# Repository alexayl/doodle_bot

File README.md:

# Doodle Bot

DoodleBot device for autonomous whiteboard management.

This repository is setup as a **monorepo** that contains the code for the different subsystems that are flashed to different devices. Please see the links below for each subsystems' README:

- [Firmware](firmware/README.md) (Alex Aylward and Jain Iftesam) is responsible for all of the code on the device.
- [CV Software](cv_software/README.md) (Trevor Antle is responsible for developing the Computer Vision application
- [Pathfinding](pathfinding/README.md) (Tom Concannon) is responsible for the path generation algorithm

## Setup

### Docs

Requirements: graphviz

### Firmware

_Note: If you are on a PC, Zephyr does not work well with WSL. Please use Windows native, or consider eventually dual-booting/VM linux!_

1. Install prerequisites

    - [Python3](https://www.geeksforgeeks.org/python/download-and-install-python-3-latest-version/)

    - Complete **only** the [Install Dependencies](https://docs.zephyrproject.org/latest/develop/getting_started/index.html#install-dependencies) section of the [Getting Started Guide](https://docs.zephyrproject.org/latest/develop/getting_started/index.html#getting-started-guide).

    - [Just command runner](https://github.com/casey/just?tab=readme-ov-file#installation) - This is used like a makefile as a hotkey for all of our project-specific commands
        - If you are using Windows, installing chocolatey package manager is recommended. After installing chocolatey, you can install just by running `choco install just`.
        - If you are on Mac, use the [Homebrew](https://brew.sh/) command `brew install just`.

If building/flsahing for [nrf52840 dk](https://docs.zephyrproject.org/latest/boards/nordic/nrf52840dk/doc/index.html):
    - SEGGER J-Link DLL
    - nrfutil (there is a python lib that allegedly has it; I needed to install it from the website though due to python dependency version conflicts)
    - 
2. Clone this repository:
    ```bash
    git clone git@github.com:alexayl/doodle_bot.git
    cd doodle_bot
    ```

3. Create and activate a Python virtual environment:
    ```bash
    python -m venv .venv
    
    source .venv/bin/activate     # Linux/macOS
    .venv\Scripts\activate.bat    # PC, Command Prompt
    .venv\Scripts\Activate.ps1    # PC, Powershell
    source .venv/Scripts/activate # PC. Git bash
    ```

4. Install west
    ```bash
    pip install west
    ```

5. Update the workspace
    ```bash
    cd firmware
    west update
    west packages pip --install
    ```

6. Install the Zephyr SDK
    1. navigate to `doodle_bot/firmware/zephyr`
        ```bash
        cd zephyr
        ```
    2.  Perform installation 
        ```bash
        west sdk install
        ```

7. Try to build and run
    1. navigate to `doodle_bot/firmware`
        ```bash
        cd ..
        ```
    2.  Build the sim to verify it works 
        ```bash
        just run-sim
        ```

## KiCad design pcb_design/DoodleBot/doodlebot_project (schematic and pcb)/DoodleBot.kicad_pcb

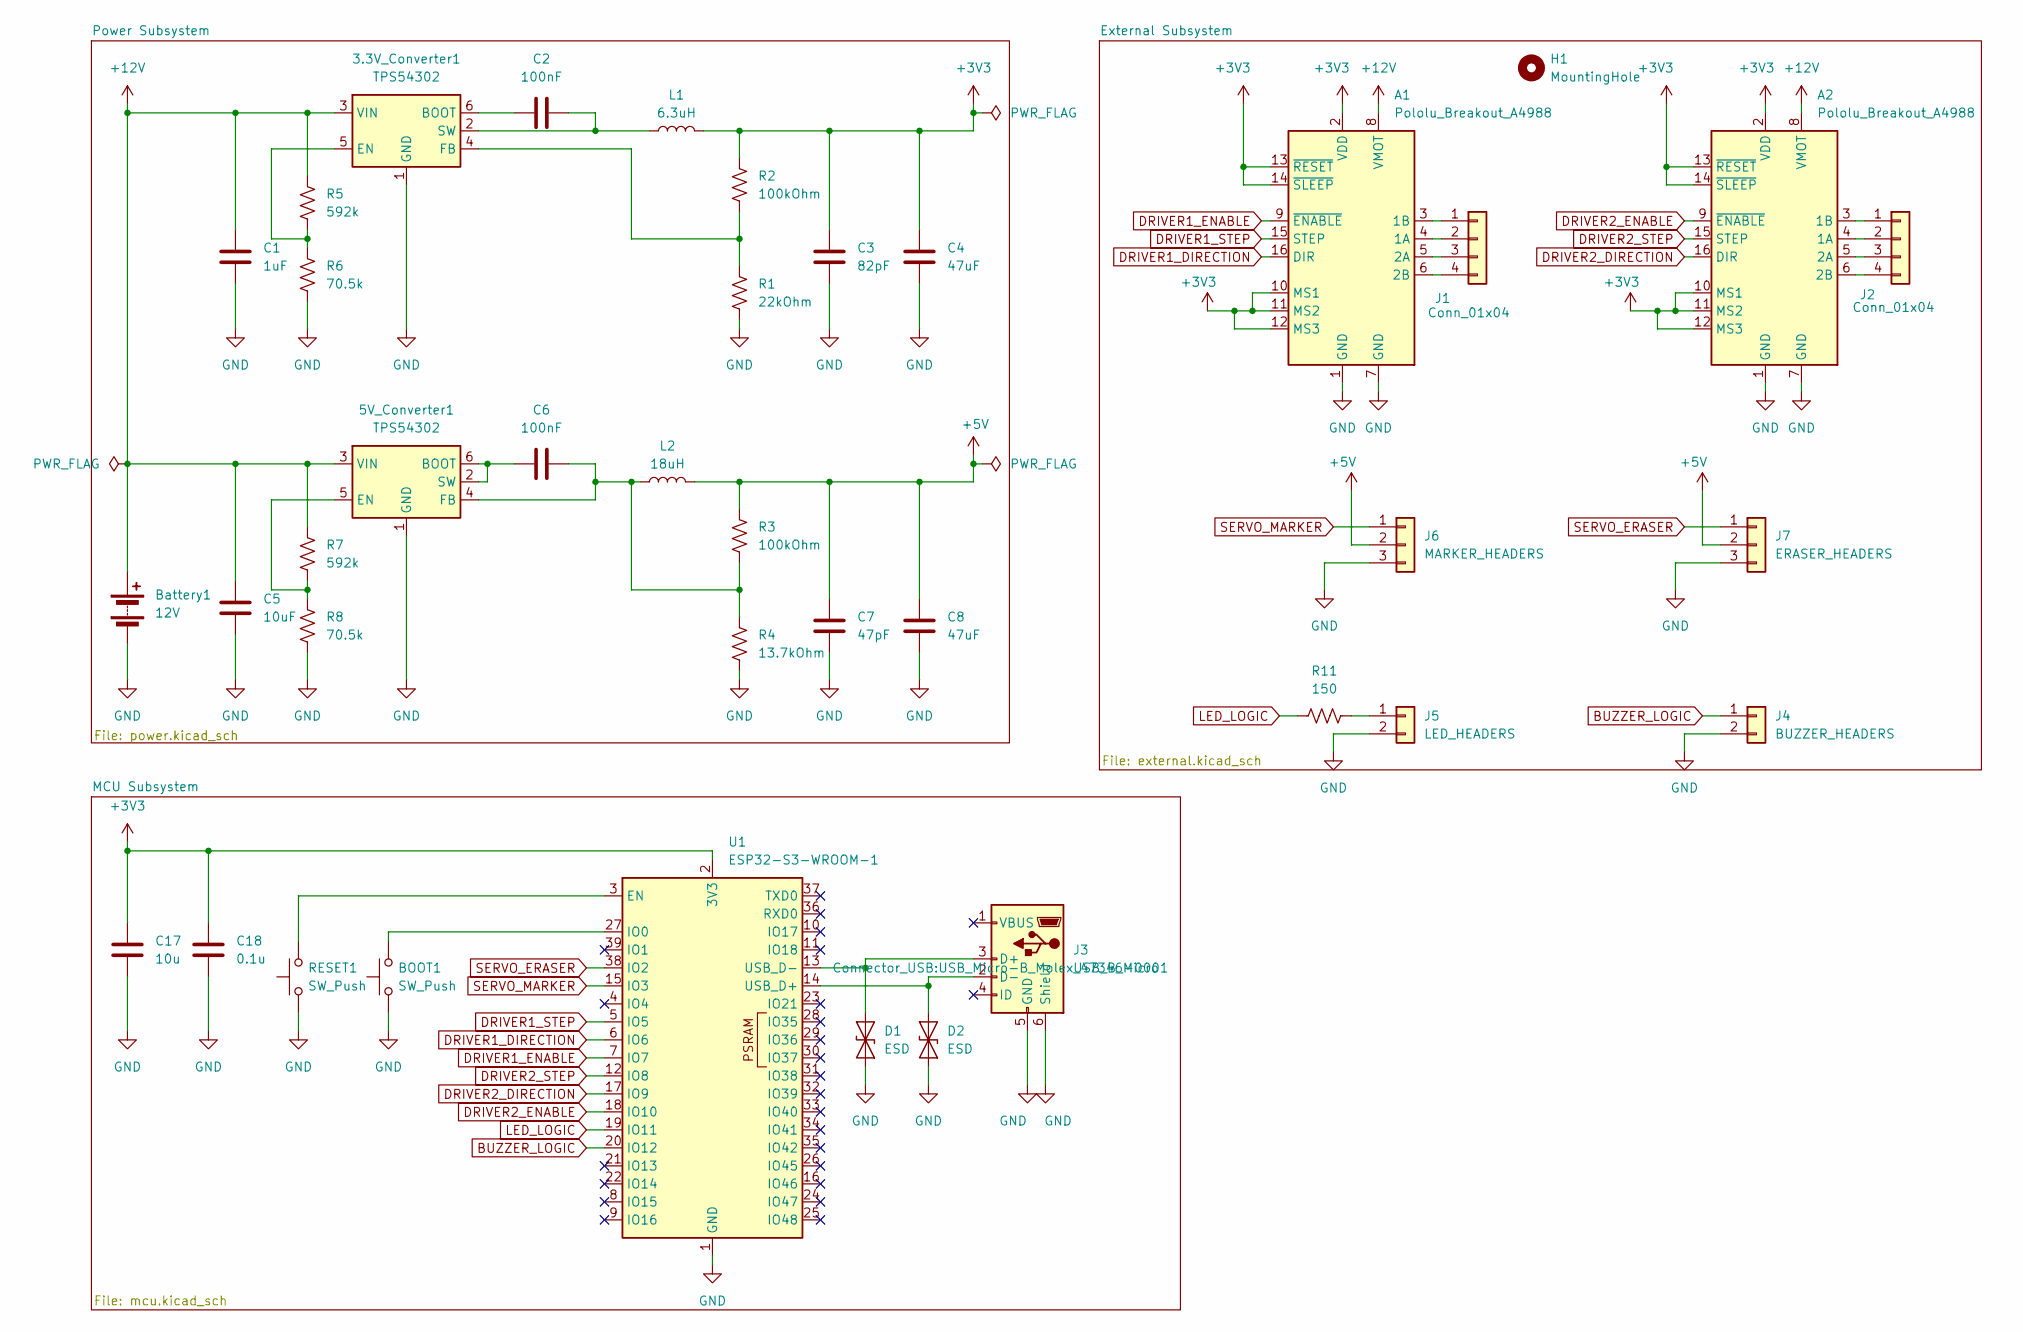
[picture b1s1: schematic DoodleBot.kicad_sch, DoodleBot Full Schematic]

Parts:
3.3V_Converter1, 5V_Converter1: TPS54302; SOT-23-6
A1, A2: Pololu_Breakout_A4988; Pololu_Breakout-16_15.2x20.3mm
BOOT1: SW_Push; SW_SPST_PTS647_Sx38
Battery1: 12V; PinHeader_1x02_P2.54mm_Vertical
C1: 1uF; C_0603_1608Metric
C2, C6: 100nF; C_0603_1608Metric
C3: 82pF; C_0603_1608Metric
C4, C8: 47uF; C_0603_1608Metric
C5: 10uF; C_0603_1608Metric
C7: 47pF; C_0603_1608Metric
C17: 10u; C_0603_1608Metric
C18: 0.1u; C_0603_1608Metric
D1, D2: ESD; D_0603_1608Metric
H1: MountingHole; MountingHole_2mm
J1, J2: Conn_01x04; PinHeader_1x04_P2.54mm_Vertical
J3: USB_B_Micro; USB_Micro-B_Molex_47346-0001
J4: BUZZER_HEADERS; PinHeader_1x02_P2.54mm_Vertical
J5: LED_HEADERS; PinHeader_1x02_P2.54mm_Vertical
J6: MARKER_HEADERS; PinHeader_1x03_P2.54mm_Vertical
J7: ERASER_HEADERS; PinHeader_1x03_P2.54mm_Vertical
L1: 6.3uH; L_Radial_D6.0mm_P4.00mm
L2: 18uH; L_Radial_D6.0mm_P4.00mm
R1: 22kOhm; R_0603_1608Metric
R2, R3: 100kOhm; R_0603_1608Metric
R4: 13.7kOhm; R_0603_1608Metric
R5, R7: 592k; R_0603_1608Metric
R6, R8: 70.5k; R_0603_1608Metric
R11: 150; R_0603_1608Metric
RESET1: SW_Push; SW_SPST_PTS647_Sx38
U1: ESP32-S3-WROOM-1

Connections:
+3V3: A1.2 (VDD), A1.10 (MS1), A1.11 (MS2), A1.12 (MS3), A1.13 (~RESET), A1.14 (~SLEEP), A2.2 (VDD), A2.10 (MS1), A2.11 (MS2), A2.12 (MS3), A2.13 (~RESET), A2.14 (~SLEEP), C3.2, C4.2, C17.1, C18.1, L1.2, R2.1, U1.2 (3V3)
+5V: C7.2, C8.2, J6.2, J7.2, L2.2, R3.1
+12V: 3.3V_Converter1.3 (VIN), 5V_Converter1.3 (VIN), A1.8 (VMOT), A2.8 (VMOT), Battery1.1 (+), C1.1, C5.1, R5.1, R7.1
BUZZER_LOGIC: J4.1, U1.20 (IO12)
DRIVER1_DIRECTION: A1.16 (DIR), U1.6 (IO6)
DRIVER1_ENABLE: A1.9 (~ENABLE), U1.7 (IO7)
DRIVER1_STEP: A1.15 (STEP), U1.5 (IO5)
DRIVER2_DIRECTION: A2.16 (DIR), U1.17 (IO9)
DRIVER2_ENABLE: A2.9 (~ENABLE), U1.18 (IO10)
DRIVER2_STEP: A2.15 (STEP), U1.12 (IO8)
GND: 3.3V_Converter1.1 (GND), 5V_Converter1.1 (GND), A1.1 (GND), A1.7 (GND), A2.1 (GND), A2.7 (GND), BOOT1.1, Battery1.2 (-), C1.2, C3.1, C4.1, C5.2, C7.1, C8.1, C17.2, C18.2, D1.1 (A1), D2.1 (A1), J3.5 (GND), J3.6 (Shield), J4.2, J5.2, J6.3, J7.3, R1.2, R4.2, R6.2, R8.2, RESET1.1, U1.1 (GND), U1.40 (GND), U1.41 (GND)
LED_LOGIC: R11.1, U1.19 (IO11)
unnamed: 3.3V_Converter1.6 (BOOT), C2.1
unnamed: 3.3V_Converter1.5 (EN), R5.2, R6.1
unnamed: 3.3V_Converter1.4 (FB), R1.1, R2.2
unnamed: 3.3V_Converter1.2 (SW), C2.2, L1.1
unnamed: 5V_Converter1.2 (SW), 5V_Converter1.6 (BOOT), C6.1
unnamed: 5V_Converter1.5 (EN), R7.2, R8.1
unnamed: 5V_Converter1.4 (FB), C6.2, L2.1, R3.2, R4.1
unnamed: A1.4 (1A), J1.2
unnamed: A1.3 (1B), J1.1
unnamed: A1.5 (2A), J1.3
unnamed: A1.6 (2B), J1.4
unnamed: A2.4 (1A), J2.2
unnamed: A2.3 (1B), J2.1
unnamed: A2.5 (2A), J2.3
unnamed: A2.6 (2B), J2.4
unnamed: D1.2 (A2), J3.3 (D+), U1.13 (USB_D-)
unnamed: D2.2 (A2), J3.2 (D-), U1.14 (USB_D+)
unnamed: J5.1, R11.2
unnamed: RESET1.2, U1.3 (EN)
unnamed: BOOT1.2, U1.27 (IO0)
SERVO_ERASER: J7.1, U1.38 (IO2)
SERVO_MARKER: J6.1, U1.15 (IO3)

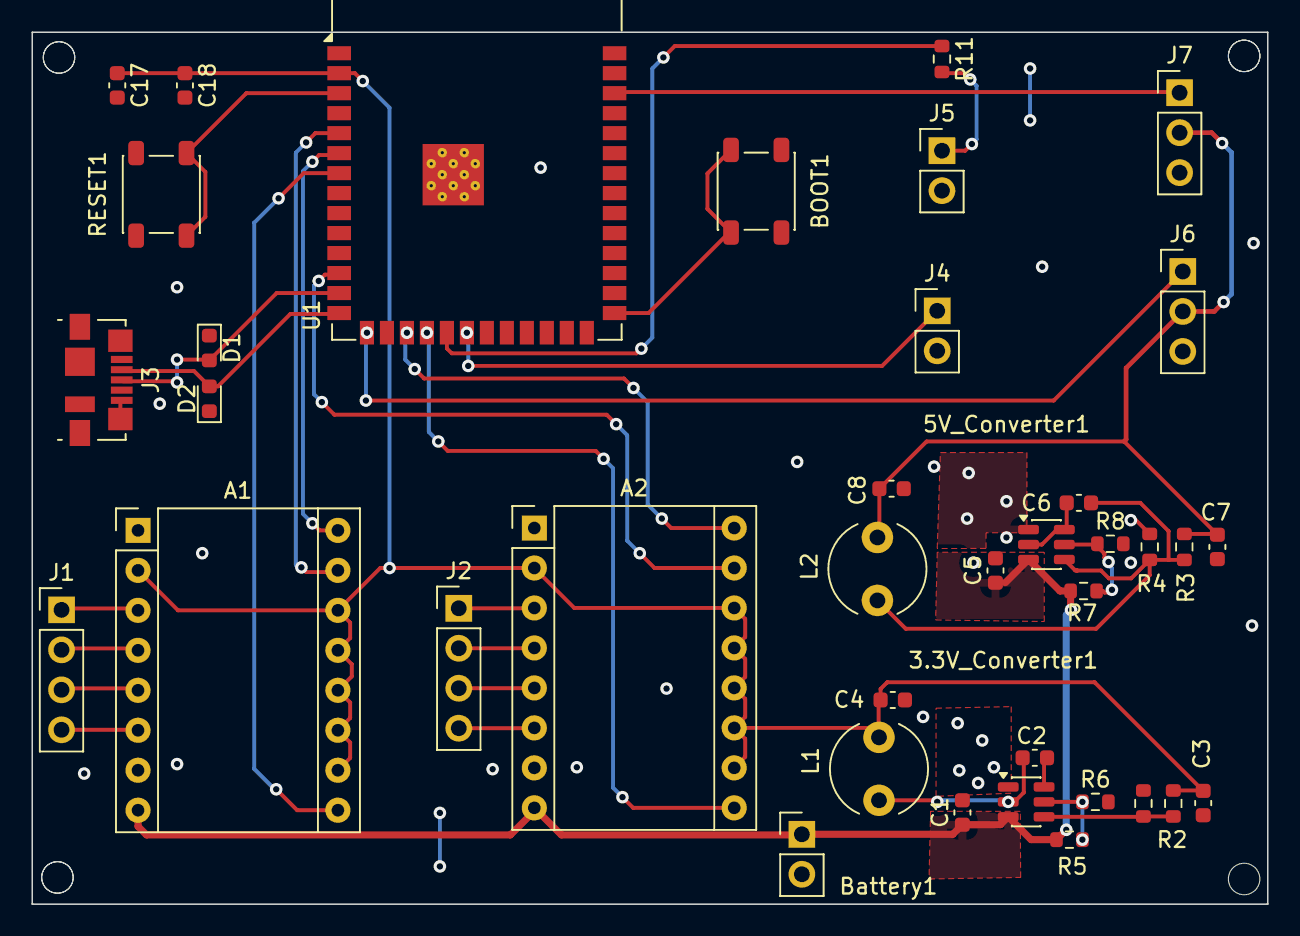
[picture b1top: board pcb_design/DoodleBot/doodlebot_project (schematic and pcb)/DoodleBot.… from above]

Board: 2 copper layers, 78.5 x 55.4 mm, 38 parts (0 on the bottom side), 34 nets.

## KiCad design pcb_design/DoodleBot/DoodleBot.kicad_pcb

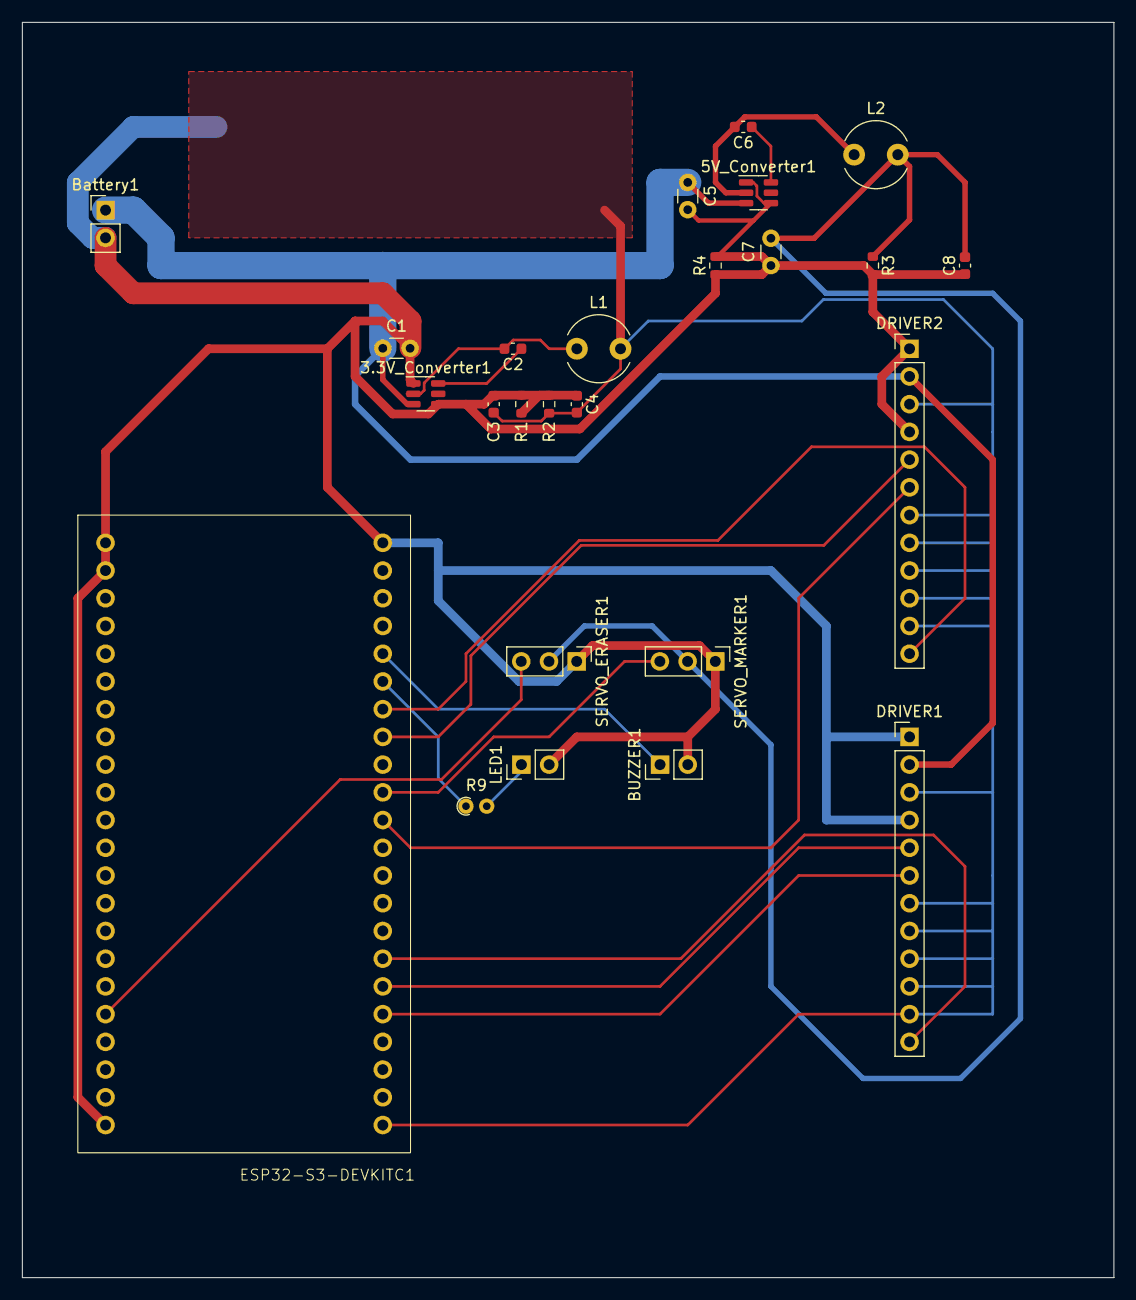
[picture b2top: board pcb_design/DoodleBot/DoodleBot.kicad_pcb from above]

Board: 2 copper layers, 100.0 x 115.0 mm, 25 parts (0 on the bottom side), 19 nets.

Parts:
3.3V_Converter1, 5V_Converter1: TPS54302; SOT-23-6
BUZZER1: Conn_01x02_Pin; PinHeader_1x02_P2.54mm_Vertical
Battery1: 12V; PinHeader_1x02_P2.54mm_Vertical
C1: 1uF; C_Disc_D3.0mm_W1.6mm_P2.50mm
C2, C6: 100nF; C_0603_1608Metric
C3: 82pF; C_0603_1608Metric
C4, C8: 47uF; C_0603_1608Metric
C5: 10uF; C_Disc_D3.0mm_W1.6mm_P2.50mm
C7: 47pF; C_Disc_D3.0mm_W1.6mm_P2.50mm
DRIVER1, DRIVER2: Conn_01x12_Pin; PinHeader_1x12_P2.54mm_Vertical
ESP32-S3-DEVKITC1: ESP32-S3-DEVKITC
L1: 6.3uH; L_Radial_D6.0mm_P4.00mm
L2: 18uH; L_Radial_D6.0mm_P4.00mm
LED1: Conn_01x02_Pin; PinHeader_1x02_P2.54mm_Vertical
R1: 22kOhm; R_0603_1608Metric
R2, R3: 100kOhm; R_0603_1608Metric
R4: 13.7kOhm; R_0603_1608Metric
R9: 150Ohm; R_Axial_DIN0204_L3.6mm_D1.6mm_P1.90mm_Vertical
SERVO_ERASER1: Conn_01x03_Pin; PinHeader_1x03_P2.54mm_Vertical
SERVO_MARKER1: Conn_01x03_Pin; PinHeader_1x03_P2.54mm_Vertical

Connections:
12V_POWER: 3.3V_Converter1.3 (VIN), 5V_Converter1.3 (VIN), Battery1.1 (+), C1.1, C5.1, DRIVER1.2, DRIVER2.2
BUZZER_GND: 3.3V_Converter1.1 (GND), 3.3V_Converter1.4 (FB), 5V_Converter1.1 (GND), 5V_Converter1.4 (FB), BUZZER1.2, Battery1.2 (-), C1.2, C3.1, C4.1, C5.2, C7.1, C8.1, DRIVER1.1, DRIVER1.4, DRIVER2.1, DRIVER2.4, ESP32-S3-DEVKITC1.22 (GND), ESP32-S3-DEVKITC1.23 (GND), ESP32-S3-DEVKITC1.24 (GND), ESP32-S3-DEVKITC1.44 (GND), LED1.2, R1.1, R1.2, R2.2, R3.2, R4.1, R4.2, SERVO_ERASER1.1, SERVO_MARKER1.1
BUZZER_LOGIC: BUZZER1.1, ESP32-S3-DEVKITC1.18 (GPIO12)
D1_MS1 (3.3V): C3.2, C4.2, DRIVER1.3, DRIVER1.7, DRIVER1.8, DRIVER1.9, DRIVER1.10, DRIVER1.11, DRIVER2.3, DRIVER2.7, DRIVER2.8, DRIVER2.9, DRIVER2.10, DRIVER2.11, ESP32-S3-DEVKITC1.1 (3V3), L1.2, R2.1
DRIVER1_DIRECTION: DRIVER1.5, ESP32-S3-DEVKITC1.6 (GPIO6)
DRIVER1_ENABLE: DRIVER1.12, ESP32-S3-DEVKITC1.7 (GPIO7)
DRIVER1_STEP: DRIVER1.6, ESP32-S3-DEVKITC1.5 (GPIO5)
DRIVER2_DIRECTION: DRIVER2.5, ESP32-S3-DEVKITC1.15 (GPIO9)
DRIVER2_ENABLE: DRIVER2.12, ESP32-S3-DEVKITC1.16 (GPIO10)
DRIVER2_STEP: DRIVER2.6, ESP32-S3-DEVKITC1.12 (GPIO8)
LED_LOGIC: ESP32-S3-DEVKITC1.17 (GPIO11), R9.1
unnamed: 3.3V_Converter1.6 (BOOT), C2.1
unnamed: 3.3V_Converter1.2 (SW), C2.2, L1.1
unnamed: 5V_Converter1.6 (BOOT), C6.1
unnamed: 5V_Converter1.2 (SW), C6.2, L2.1
unnamed: LED1.1, R9.2
unnamed: C7.2, C8.2, L2.2, R3.1, SERVO_ERASER1.2, SERVO_MARKER1.2
SERVO_ERASER: ESP32-S3-DEVKITC1.40 (GPIO2), SERVO_ERASER1.3
SERVO_MARKER: ESP32-S3-DEVKITC1.13 (GPIO3), SERVO_MARKER1.3

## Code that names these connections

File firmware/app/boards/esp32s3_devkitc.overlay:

/ {
    /* Servo motor for eraser control - GPIO4 PWM */
    servo_eraser: servo_eraser {
        compatible = "doodle-servo";
        pwms = <&ledc0 0 20000000 0>; /* 20ms period, normal polarity - GPIO4 */
        label = "SERVO_ERASER";
    };

    /* Servo motor for marker control - GPIO15 PWM */
    servo_marker: servo_marker {
        compatible = "doodle-servo";
        pwms = <&ledc0 1 20000000 0>; /* 20ms period, normal polarity - GPIO15 */
        label = "SERVO_MARKER";
    };

    /* Left stepper motor via A4988 driver */
    stepper_left: stepper_left {
        compatible = "stepper-driver";
        step-gpio = <&gpio0 5 GPIO_ACTIVE_HIGH>;      /* GPIO5 - Step pulses */
        direction-gpio = <&gpio0 6 GPIO_ACTIVE_HIGH>; /* GPIO6 - Direction control */
        enable-gpio = <&gpio0 7 GPIO_ACTIVE_LOW>;     /* GPIO7 - Enable/disable */
        label = "LEFT_STEPPER";
        steps-per-revolution = <200>;
        microsteps = <16>;            /* Fixed 1/16 microstepping (hardwired) */
        max-speed = <3200>;           /* Max steps/sec (with microstepping) */
        acceleration = <1000>;        /* Steps/sec² */
    };

    /* Right stepper motor via A4988 driver */
    stepper_right: stepper_right {
        compatible = "stepper-driver";
        step-gpio = <&gpio0 8 GPIO_ACTIVE_HIGH>;      /* GPIO8 - Step pulses */
        direction-gpio = <&gpio0 9 GPIO_ACTIVE_HIGH>; /* GPIO9 - Direction control */
        enable-gpio = <&gpio0 10 GPIO_ACTIVE_LOW>;    /* GPIO10 - Enable/disable */
        label = "RIGHT_STEPPER";
        steps-per-revolution = <200>;
        microsteps = <16>;            /* Fixed 1/16 microstepping (hardwired) */
        max-speed = <3200>;           /* Max steps/sec (with microstepping) */
        acceleration = <1000>;        /* Steps/sec² */
    };

    /* GPIO LED configuration */
    leds {
        compatible = "gpio-leds";
        led1: led_1 {
            gpios = <&gpio0 11 GPIO_ACTIVE_HIGH>; /* GPIO11 - Status LED */
            label = "STATUS_LED";
        };
    };

    /* GPIO Buzzer configuration */
    buzzer: buzzer {
        compatible = "gpio-buzzer";
        gpios = <&gpio0 12 GPIO_ACTIVE_HIGH>; /* GPIO12 - Buzzer */
        label = "BUZZER";
    };

    aliases {
        stepper-left = &stepper_left;
        stepper-right = &stepper_right;
        servo-eraser = &servo_eraser;
        servo-marker = &servo_marker;
        led0 = &led1;
        buzzer0 = &buzzer;
    };
};

&ledc0 {
    status = "okay";
    pinctrl-0 = <&ledc0_default>;
    pinctrl-names = "default";
    #pwm-cells = <3>;
};

&pinctrl {
    ledc0_default: ledc0_default {
        group1 {
            pinmux = <LEDC_CH0_GPIO4>,   /* GPIO4 - Servo Eraser PWM */
                     <LEDC_CH1_GPIO15>;  /* GPIO15 - Servo Marker PWM */
            output-enable;
        };
    };
};

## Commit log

2025-08-29 Create LICENSE
2025-09-02 initial
2025-09-02 get output from esp32
2025-09-02 update dir names and instructions
2025-09-06 template
2025-09-06 update file structure
2025-09-08 create comms and state threads
2025-09-13 fix intellisense
2025-09-13 move state thread to state_task
2025-09-13 add scaffolding for state machine diagram
2025-09-13 update rest of app for c++
2025-09-13 Setup state-machine framework
2025-09-13 Write state machine tests
2025-09-13 add tests to justfile
2025-09-13 reformat docs
2025-09-16 Add support for nrf52840 dk
2025-09-16 nrf52840 dk instructions
2025-09-16 pt 2
2025-09-16 Scaffolding for coms->nav
2025-09-16 web interface v0
2025-09-18 vsc config
2025-09-18 update diagrams
2025-09-18 nrf52840 sanity check
2025-09-18 scaffolding for next part
2025-09-18 requirements.txt
2025-09-23 pathfinding skeleton
2025-09-25 pathfinding skeleton + v0 model
2025-09-30 img2graph v0
2025-09-30 .gitignore update
2025-09-30 updated state machine
2025-10-01 First draft of servo driver - WORKING!
2025-10-02 img2graph updates
2025-10-02 cleaned + commented graph2path
2025-10-02 Added Servo Driver in tests/
2025-10-06 img2graph cleanup
2025-10-06 Incorporated already-created led_gpio driver with my application layer code!
2025-10-07 Alex do you believe in global warming?
2025-10-07 comment removed
2025-10-07 max nodes size
2025-10-07 Recursive README skeleton
2025-10-07 collinearity_pruning
2025-10-08 Update Pathfinding subsystem description in README
    Clarified the responsibility of the Pathfinding subsystem.
2025-10-08 img2graph.py return endpoints
2025-10-08 Enhance README with pathfinding algorithm details
    Expanded the README to include detailed explanations of the pathfinding algorithm, its features, installation instructions, and usage scenarios.
2025-10-08 Drafted Stepper Motor Driver Revision #1
2025-10-09 Updated Driver README
2025-10-09 Fix CV Software description in README
    Corrected the description for the CV Software subsystem.
2025-10-09 Enhance README with detailed project information
2025-10-09 working v1 for demo
2025-10-09 Included error handling
2025-10-09 cv reqs
2025-10-09 Add requirements.txt with necessary dependencies
2025-10-10 graph2path done
2025-10-11 move cam code and bt framework
2025-10-11 Got Buzzer, LED, and servo motor work on ESP32. Was missing a LEDC configuration in devicetree.
2025-10-12 fixed incorporating the servo with the servo driver
2025-10-12 Got Dual Servos to work in Zephyr!
2025-10-12 Updated README for Packaging Review
2025-10-12 Fixed Typos for packaging review
2025-10-12 almost done for package
2025-10-13 Add PCB Folder
2025-10-13 Added PCB schematic
2025-10-13 cv done for now
2025-10-13 user error
2025-10-13 camera settings
2025-10-13 camera optimizations
2025-10-13 boardtobot
2025-10-13 Created working test case for PWM Buzzer
2025-10-13 Stepper Motor test working!
2025-10-14 path2gcode
2025-10-14 sim working
2025-10-14 main file created
2025-10-14 server changes
2025-10-14 Made demo test file
2025-10-15 path fix for gcode
2025-10-15 init ble
2025-10-15 update readmes
2025-10-15 move app tests to tests/app
2025-10-15 ble class proven working
2025-10-15 functioning BLE/instruction parsing
2025-10-15 Incorporated Stepper Motor and Servo motor changes.
2025-10-15 working on nav
2025-10-15 Fixed servo and LED configuration
2025-10-15 gcode parsing overview
2025-10-15 updated gcode formulation
2025-10-16 add nav py test
2025-10-16 specs 1 and 2 working
2025-10-16 spec 3 test working
2025-10-16 build-nrf working after jain changes
2025-10-17 midterm demo
2025-10-21 just generic test template for drivers
2025-10-21 Pushing condensed Justfile
2025-10-23 test ble comms for trevor
2025-10-23 Pushing condensed justfile into master
2025-10-23 ble integration and cv enhance
2025-10-23 ble cleanup
2025-10-23 more reqs
2025-10-23 readme update
2025-10-23 gocde parsing with ack/nack
2025-10-23 Refactored the code!
2025-10-23 update ble, comms, and instruction parser
2025-10-24 misc cleans
2025-10-24 remove crap from nav
2025-10-24 app: fix compilation errors
2025-10-24 Compiled changes
2025-10-24 Compiled changes 2.0
2025-10-24 starting unit testing
2025-10-24 still testing nav
2025-10-24 stepper wrapper building
2025-10-24 rest of wrappers building
2025-10-25 Incorporated dual stepper functionality. Will need to fix why it is moving forward when it should be moving backward.
2025-10-27 better main
2025-10-28 reduce some code
2025-10-28 in mvp class
2025-10-28 send packets -> send packet
2025-10-28 Fully added and tested multi-stepper motor functionality!
2025-10-28 better code
2025-10-28 working sending packets
2025-10-28 working for short transmissions, fixing for long
2025-10-28 debugging motor navigation to motor control and high frequency ble transmission
2025-10-29 fix parsing issues, parse large files
2025-10-30 working for longer transmissions
2025-10-30 sending good packets
2025-10-30 two steppers driving
2025-10-30 cleaning up prink statements
2025-10-30 cleaned up ble python script
2025-10-30 firmware for lil t
2025-10-30 update script
2025-10-30 initial cv
2025-10-30 Added Stepper enable functionality
2025-10-30 tmp2
2025-10-30 working ble
2025-10-30 Update NRF_PORT for non-Windows systems
2025-11-01 updated kinematics and documentation
2025-11-04 fw: update overlays so nrf builds and old esp32 one removed
2025-11-04 fw: remove unnecessary files
2025-11-04 fw: building but untested
2025-11-04 fw: ble rate limiting working
2025-11-05 doesnt work
2025-11-06 ble send mutex
2025-11-06 yahooo
2025-11-06 integrated
2025-11-06 fw: INCOMPLETE working on state machine changes
2025-11-11 remove unused function
2025-11-12 Changed left stepper motor orientation
2025-11-13 remove pristine builds for time
2025-11-13 Add Project Files
2025-11-13 stepper active idle
2025-11-14 Connor's version
2025-11-17 Jain's PCB! (The project is in its own folder)
2025-11-17 Connor's Revisions #4!
2025-11-17 Reorganized project structure
2025-11-17 Added wider 12V traces from 0.39mm to 0.45mm
2025-11-18 init branch
2025-11-18 working absolute position
2025-11-18 working relative
2025-11-18 add comment support
2025-11-18 servo builds
2025-11-18 servo work but not stepper?
2025-11-18 add g1 tests
2025-11-18 hardware init sequence
2025-11-19 nothing works and i am sad
2025-11-20 homing mostly works
2025-11-23 fw: new body dropped
2025-11-23 fw: refactor ble tests
2025-11-23 better waypoint and deviation computation, board match pathfinding
2025-12-01 fix import issue
2025-12-01 correction working better
2025-12-02 start from starting position
2025-12-03 small tweak
2025-12-03 some optimizations
2025-12-03 oopsies
2025-12-03 Implement BLE connection handling and advertising restart logic in BleService; add servo angle command support in GCode processing.
2025-12-03 Add comms_reset function to reset parser state on BLE disconnect; update BLE service to call this function. Adjusted GCode handling to use global parser instance.
2025-12-04 fw: add more tests
2025-12-04 fw: base refactor
2025-12-04 fw: fix compiler warnings
2025-12-04 smoother movement
2025-12-04 fw: updated print statements
2025-12-05 fw: acks send properly
2025-12-05 fw: acks part 2
2025-12-05 fw: Refactor stepper motor driver to use A4988 with Zephyr's step_dir framework. Update CMake and Kconfig for new driver integration. Modify application code to utilize GPIO for step pulses instead o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
2025-12-05 fw: tuning motors
2025-12-06 granularity changes
2025-12-06 chnaged servo commands and removed comments in gcode
2025-12-06 waypoints and smudges oh my
2025-12-07 cv changes on gcode
2025-12-08 better directories and homography
2025-12-09 Refactor LED support to use custom simple_led driver instead of Zephyr's LED subsystem. Update CMakeLists.txt accordingly. Clean up unused connection event callbacks in ble_service.h and fix WHEELBAS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
2025-12-10 fw: DOO and BOO
2025-12-10 fw: update thread priorities
2025-12-10 fw: velocity smoothing implementation
2025-12-10 fw: low effort precision improvements
2025-12-10 fw: medium effort precision improvements
2025-12-10 fw: add dynamic parameter changes
2025-12-10 initial led support
2025-12-10 fw: full led and buzzer support
2025-12-10 fw: working on CHT
2025-12-11 demo day! so excited
2025-12-11 fw: midi support for buzzer
2025-12-11 fw: soft reboot when ble disconnects POC
2025-12-11 servo up/down fix
2025-12-11 sim fixes
2025-12-11 recent
2025-12-11 more padding fixes
2025-12-11 edit gitignore
2025-12-11 updated ece
